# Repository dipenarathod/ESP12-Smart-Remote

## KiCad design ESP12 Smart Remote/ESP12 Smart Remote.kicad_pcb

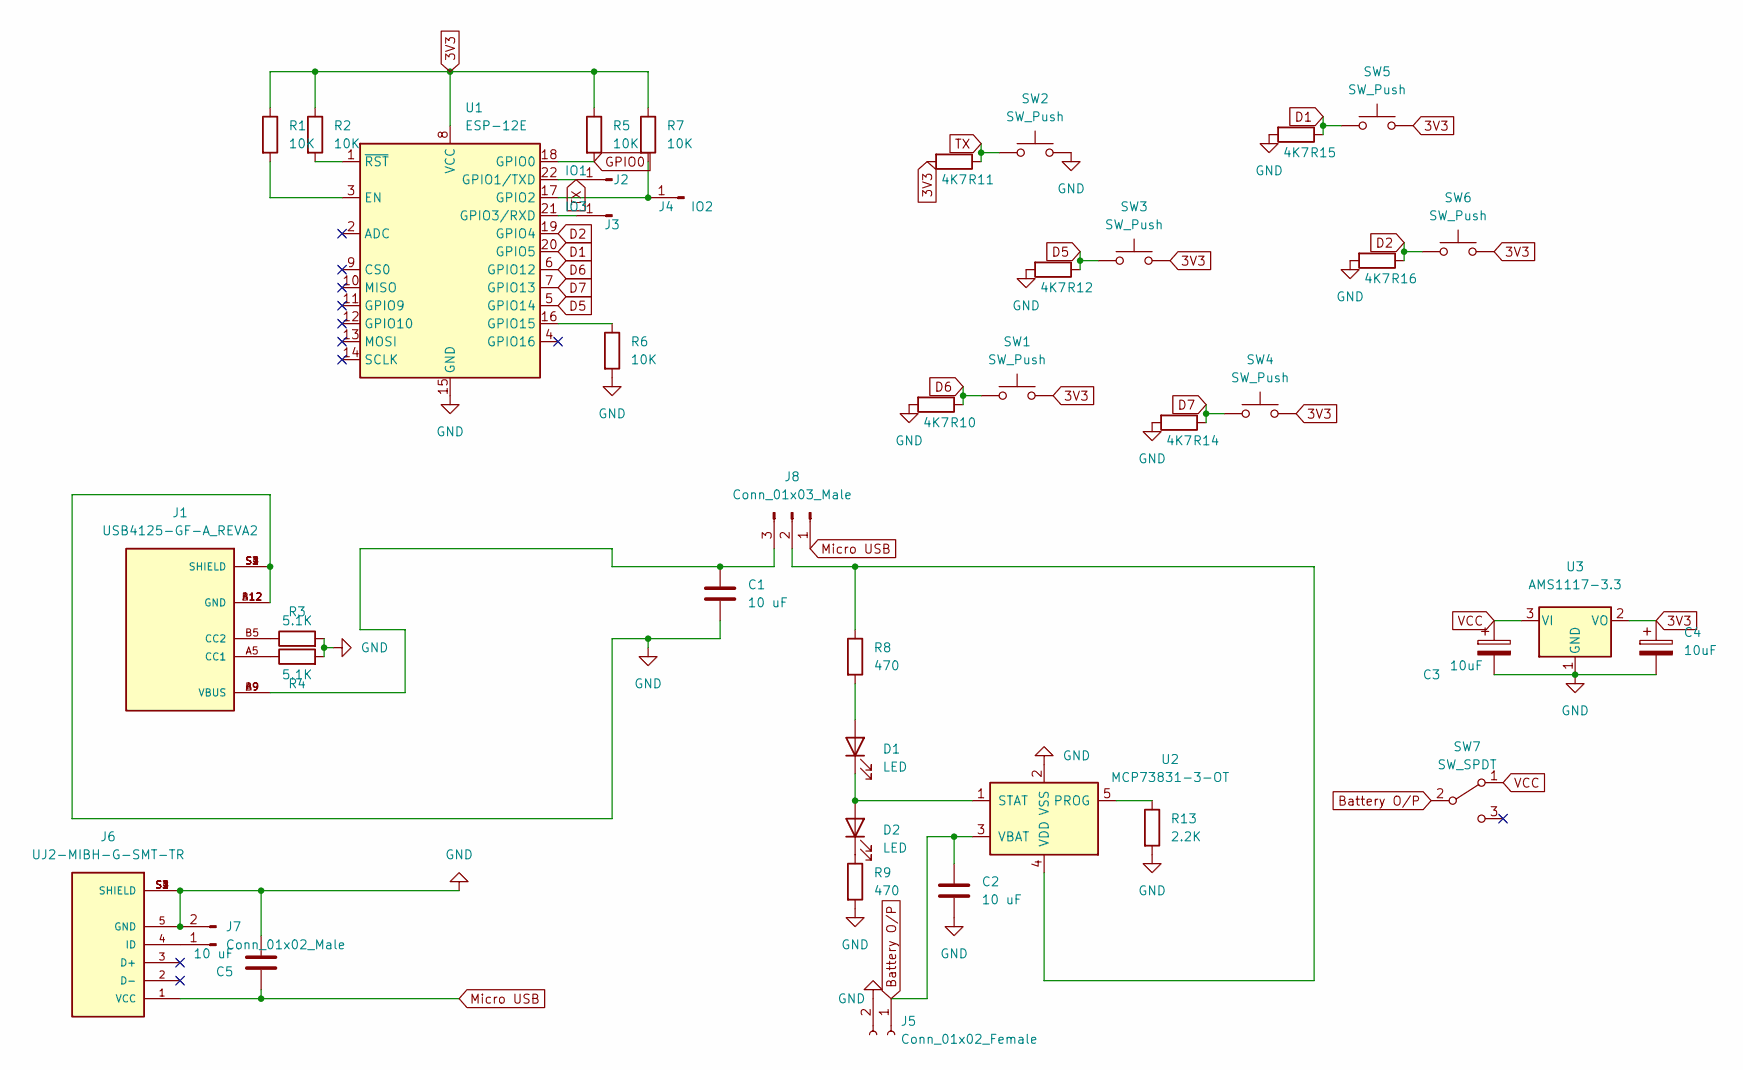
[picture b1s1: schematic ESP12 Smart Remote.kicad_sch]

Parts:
C1, C2, C5: 10 uF; C_1206_3216Metric_Pad1.33x1.80mm_HandSolder
C3, C4: 10uF; C_1206_3216Metric_Pad1.33x1.80mm_HandSolder
D1, D2: LED; LED_0805_2012Metric_Pad1.15x1.40mm_HandSolder
J1: USB4125-GF-A_REVA2; GCT_USB4125-GF-A_REVA2; PARTREV Rev A2
J2: IO1; PinHeader_1x01_P2.54mm_Vertical
J3: IO3; PinHeader_1x01_P2.54mm_Vertical
J4: IO2; PinHeader_1x01_P2.54mm_Vertical
J5: Conn_01x02_Female; PinSocket_1x02_P2.54mm_Vertical
J6: UJ2-MIBH-G-SMT-TR; CUI_UJ2-MIBH-G-SMT-TR; PARTREV 1.0
J7: Conn_01x02_Male; PinHeader_1x02_P2.54mm_Vertical
J8: Conn_01x03_Male; PinHeader_1x03_P2.54mm_Vertical
R1, R2, R5, R6, R7: 10K; R_Axial_DIN0207_L6.3mm_D2.5mm_P7.62mm_Horizontal
R3, R4: 5.1K; R_Axial_DIN0207_L6.3mm_D2.5mm_P7.62mm_Horizontal
R8, R9: 470; R_Axial_DIN0207_L6.3mm_D2.5mm_P7.62mm_Horizontal
R10, R11, R12, R14, R15, R16: 4K7; R_Axial_DIN0207_L6.3mm_D2.5mm_P7.62mm_Horizontal
R13: 2.2K; R_Axial_DIN0207_L6.3mm_D2.5mm_P7.62mm_Horizontal
SW1, SW2, SW3, SW4, SW5, SW6: SW_Push; SW_PUSH_6mm
SW7: SW_SPDT; PinHeader_1x03_P2.54mm_Vertical
U1: ESP-12E
U2: MCP73831-3-OT; SOT-23-5
U3: AMS1117-3.3; SOT-223-3_TabPin2

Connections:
3V3: C4.1, R1.1, R2.1, R5.1, R7.1, R11.2, SW1.2, SW3.2, SW4.2, SW5.2, SW6.2, U1.8 (VCC), U3.2 (VO)
Battery O/P: C2.1, J5.1, SW7.2 (B), U2.3 (VBAT)
D1: R15.1, SW5.1, U1.20 (GPIO5)
D2: R16.1, SW6.1, U1.19 (GPIO4)
D5: R12.1, SW3.1, U1.5 (GPIO14)
D6: R10.1, SW1.1, U1.6 (GPIO12)
D7: R14.1, SW4.1, U1.7 (GPIO13)
GND: C1.2, C2.2, C3.2, C4.2, C5.2, J1.A12 (GND), J1.B12 (GND), J1.S1 (SHIELD), J1.S2 (SHIELD), J1.S3 (SHIELD), J1.S4 (SHIELD), J5.2, J6.5 (GND), J6.S1 (SHIELD), J6.S2 (SHIELD), J6.S3 (SHIELD), J6.S4 (SHIELD), J7.2, R3.2, R4.2, R6.2, R9.2, R10.2, R12.2, R13.2, R14.2, R15.2, R16.2, SW2.2, U1.15 (GND), U2.2 (VSS), U3.1 (GND)
GPIO0: R5.2, U1.18 (GPIO0)
Micro USB: C5.1, J6.1 (VCC), J8.1
unnamed: C1.1, J1.A9 (VBUS), J1.B9 (VBUS), J8.3
unnamed: D1.1 (K), D2.2 (A), U2.1 (STAT)
unnamed: D1.2 (A), R8.2
unnamed: D2.1 (K), R9.1
unnamed: J1.A5 (CC1), R4.1
unnamed: J1.B5 (CC2), R3.1
unnamed: J3.1, U1.21 (GPIO3/RXD)
unnamed: J4.1, R7.2, U1.17 (GPIO2)
unnamed: J6.4 (ID), J7.1
unnamed: J8.2, R8.1, U2.4 (VDD)
unnamed: R1.2, U1.3 (EN)
unnamed: R2.2, U1.1 (~RST)
unnamed: R6.1, U1.16 (GPIO15)
unnamed: R13.1, U2.5 (PROG)
TX: J2.1, R11.1, SW2.1, U1.22 (GPIO1/TXD)
VCC: C3.1, SW7.1 (A), U3.3 (VI)

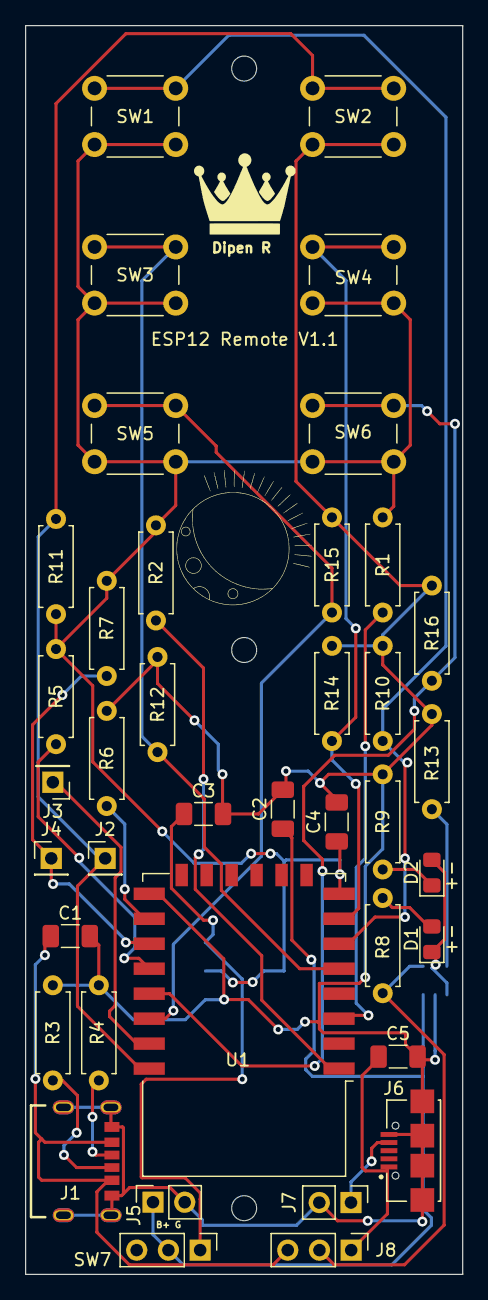
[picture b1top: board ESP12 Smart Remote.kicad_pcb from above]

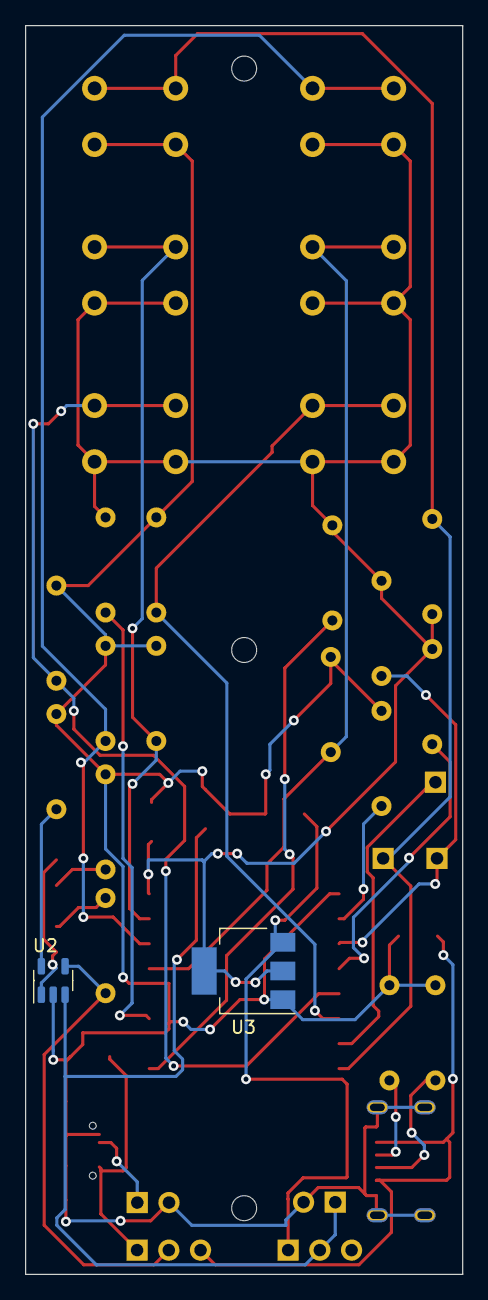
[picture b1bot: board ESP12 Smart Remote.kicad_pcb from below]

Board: 2 copper layers, 35.0 x 100.0 mm, 41 parts (2 on the bottom side), 26 nets.
